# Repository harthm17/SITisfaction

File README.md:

# SITisfaction

Diplomarbeit der HTBLA Kaindorf aus dem Schuljahr 2021/22

## Mitglieder & Aufgabenbereich

| Mitglied | Aufgabenbereich | 
| ---- | ----- 
| Adam Mike | Mechanik und Konstruktion
| Harrer Thomas | Elektrotechnik
| Pust Thomas | Softwareentwicklung - Android App

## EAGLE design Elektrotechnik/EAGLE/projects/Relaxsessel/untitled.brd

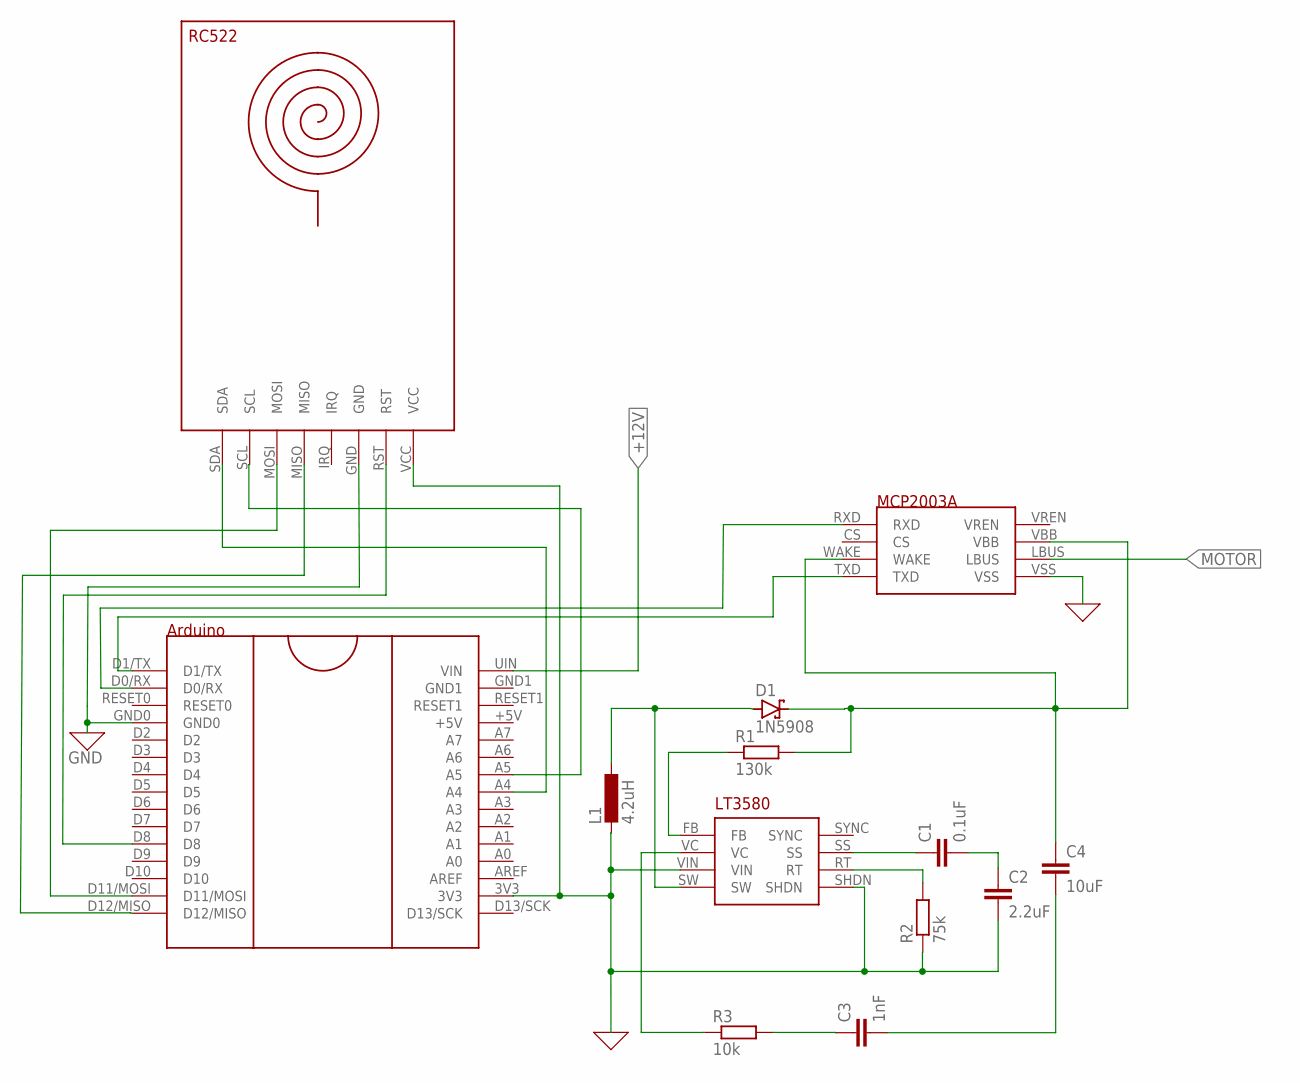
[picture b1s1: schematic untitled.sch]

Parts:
C1: 0.1uF; C075-032X103
C2: 2.2uF; C075-032X103
C3: 1nF; C075-032X103
C4: 10uF; C075-032X103
D1: 1N5908; C4111-15
L1: 4.2uH; 0207/7
R1: 130k; 0207/7
R2: 75k; 0207/7
R3: 10k; 0207/7
U$1: ARDUINO
U$2: LIN
U$3: LT3580
U$4: RC522

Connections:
0: C2.2, L1.2, R2.1, U$1.3V3, U$2.VSS, U$3.SHDN, U$3.VIN, U$4.VCC
+12V: U$1.UIN (VIN)
GND: U$1.GND0, U$4.GND
MOTOR: U$2.LBUS
unnamed: C3.1, R3.2
unnamed: C1.1, U$3.SS
unnamed: C1.2, C2.1
unnamed: U$1.A4, U$4.SDA
unnamed: R2.2, U$3.RT
unnamed: D1.A, L1.1, U$3.SW
unnamed: C4.1, D1.C, R1.2, U$2.VBB, U$2.WAKE
unnamed: R1.1, U$3.FB
unnamed: R3.1, U$3.VC
unnamed: C3.2, C4.2
unnamed: U$1.A5, U$4.SCL
unnamed: U$1.D11/MOSI, U$4.MOSI
unnamed: U$1.D12/MISO, U$4.MISO
unnamed: U$1.D8, U$4.RST
unnamed: U$1.D0/RX, U$2.RXD
unnamed: U$1.D1/TX, U$2.TXD

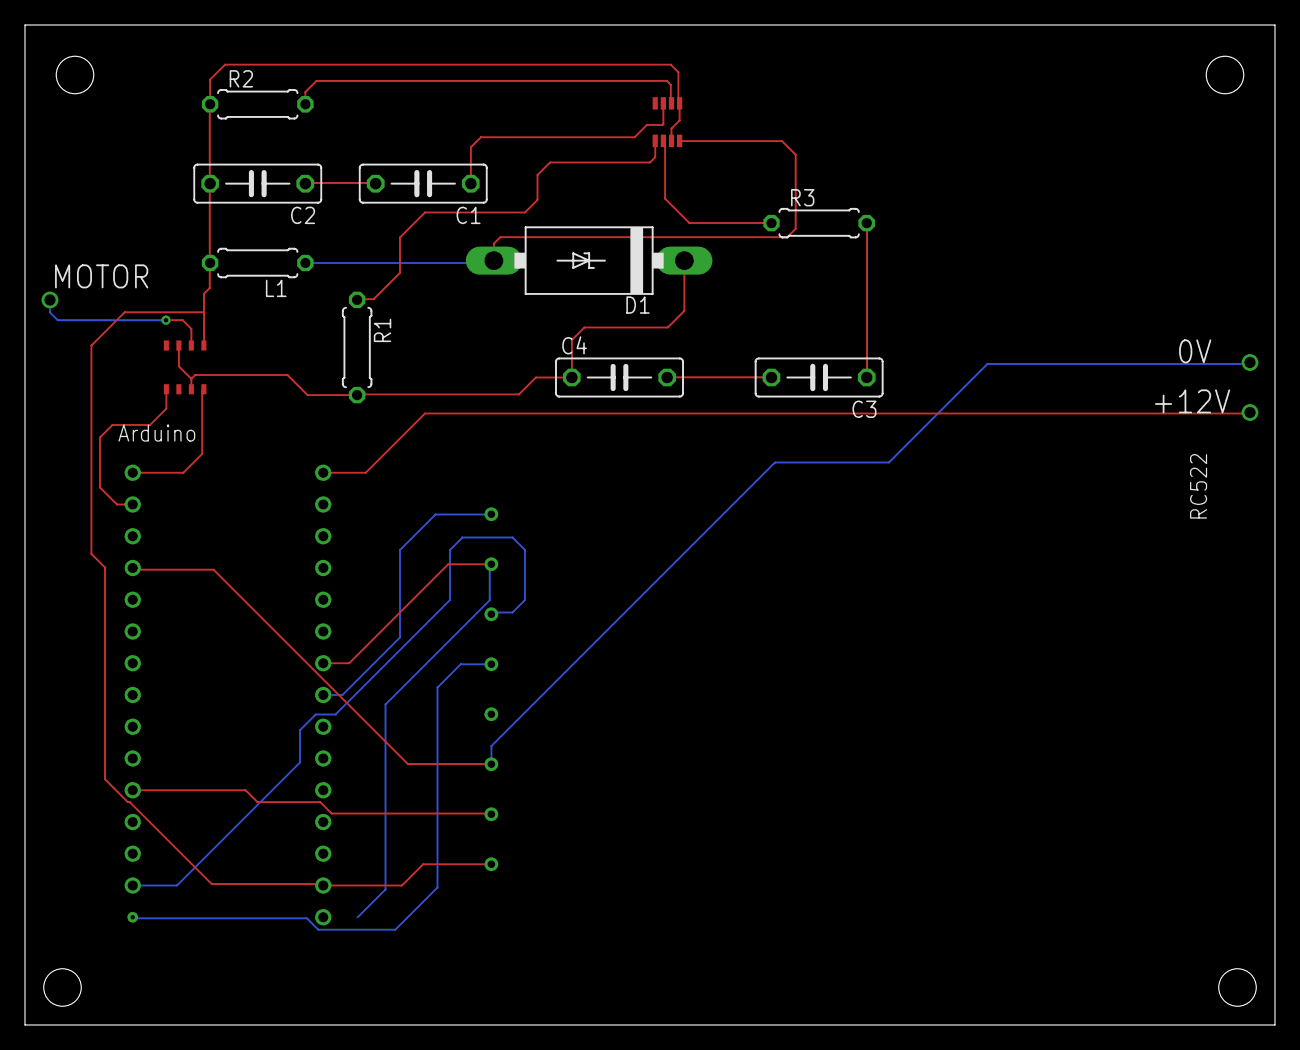
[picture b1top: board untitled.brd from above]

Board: 2 copper layers, 100.0 x 80.0 mm, 13 parts (0 on the bottom side), 18 nets.
